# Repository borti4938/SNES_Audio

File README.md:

### SNES Audio Mods
---

This is a collection of earlier projects. These projects are not under development anymore. Documentation is rather simple or simply not present

Please don't write me for any support. Please reach out to community forums and use the knowledge and experiences there.

If you want to change something on the digital audio mod, I suggest you to replace the TI-SPDIF audio encoder by CirrusLogic-SPDIF audio encoder of same size (but different pinout).

Best Regards, Peter

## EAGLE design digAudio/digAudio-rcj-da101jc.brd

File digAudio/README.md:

### IMPORTANT NOTE:

There is a bug on all PCBs manifacture before Jan 5th., 2023!
Pin 14 on the DIT4096 IC is not properly connected.
Instead of tied to GND the pin was left floating.

If you have one effected board, you can easily fix that.
Simply connect pin 14 of the DIT4096 on your PCB to GND.
This pin is a corner pin and you can use any GND pad.
This should be an easy fix.

Sorry for any inconvenience caused! 

-----------------------------------------------------------------------------------

### Solder Joints:

A mapping Pads of PCB to S-DSP/S-APU is given on the bottoms silkscreen.  
Take a picture of it if needed.

-----------------------------------------------------------------------------------

### Components:

See BOM.xlsx (use the appropriate page)  

-----------------------------------------------------------------------------------

### RCA or XLR setup

Design supports both setups. Please be refered to the notes of left in the BOM

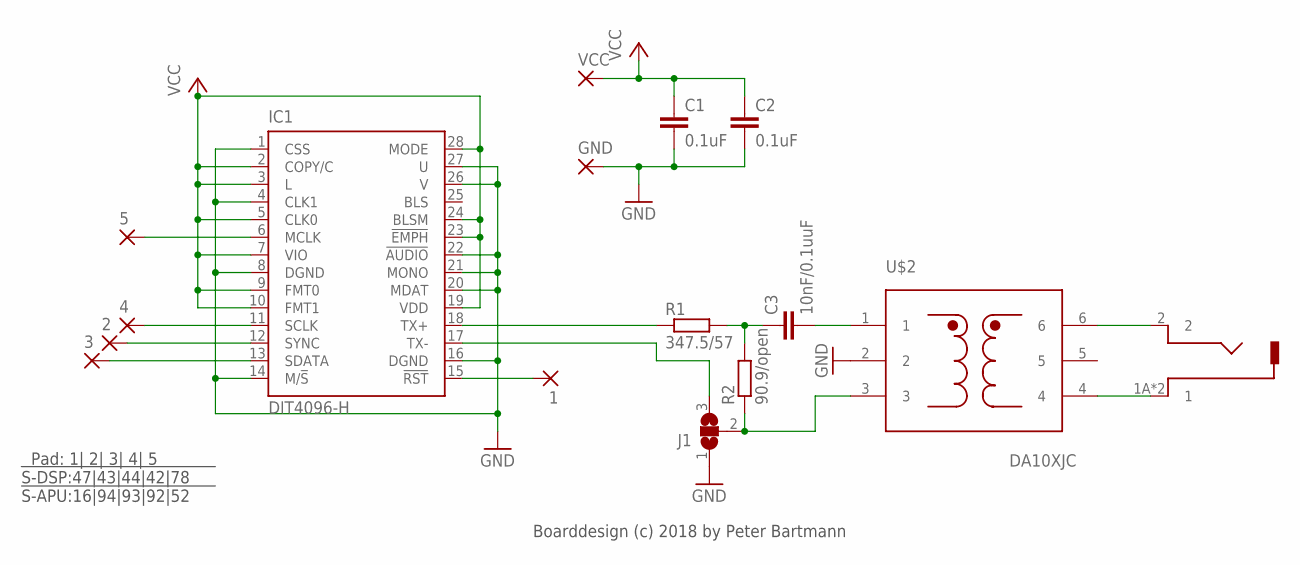
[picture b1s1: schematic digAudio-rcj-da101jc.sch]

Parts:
1, 2, 3, 4, 5: SMD1; SMD0,8-1,6
C1, C2: 0.1uF; C0603
C3: 10nF/0.1uuF; C0603
GND: 1,6/0,9
IC1: DIT4096-H; PW_R-PDSO-G28
J1: SJ2W; SJ_2
R1: 347.5/57; R0603
R2: 90.9/open; R0603
U$1: RCJ-013-SMT-TR; RCJ_01X_SMT_MODIFIED
U$2: DA10XJC; DA101JC
VCC: 1,6/0,9

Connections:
GND: C1.2, C2.2, GND.1, IC1.1 (CSS), IC1.4 (CLK1), IC1.8 (DGND), IC1.14 (M/!S), IC1.16 (DGND), IC1.20 (MDAT), IC1.21 (MONO), IC1.22 (!AUDIO), IC1.26 (V), IC1.27 (U), J1.1, U$2.2
unnamed: IC1.18 (TX+), R1.1
unnamed: 1.P$1, IC1.15 (!RST)
unnamed: 2.P$1, IC1.12 (SYNC)
unnamed: 4.P$1, IC1.11 (SCLK)
unnamed: 3.P$1, IC1.13 (SDATA)
unnamed: 5.P$1, IC1.6 (MCLK)
unnamed: IC1.17 (TX-), J1.3
unnamed: C3.1, R1.2, R2.2
unnamed: U$1.2, U$2.6
unnamed: U$1.1A (1), U$1.1B (1), U$2.4
unnamed: C3.2, U$2.1
unnamed: J1.2, R2.1, U$2.3
VCC: C1.1, C2.1, IC1.2 (COPY/C), IC1.3 (L), IC1.5 (CLK0), IC1.7 (VIO), IC1.9 (FMT0), IC1.10 (FMT1), IC1.19 (VDD), IC1.23 (!EMPH), IC1.24 (BLSM), IC1.28 (MODE), VCC.1

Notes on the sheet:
Pad: 1| 2| 3| 4| 5 S-DSP:47|43|44|42|78 S-APU:16|94|93|92|52
Boarddesign (c) 2018 by Peter Bartmann

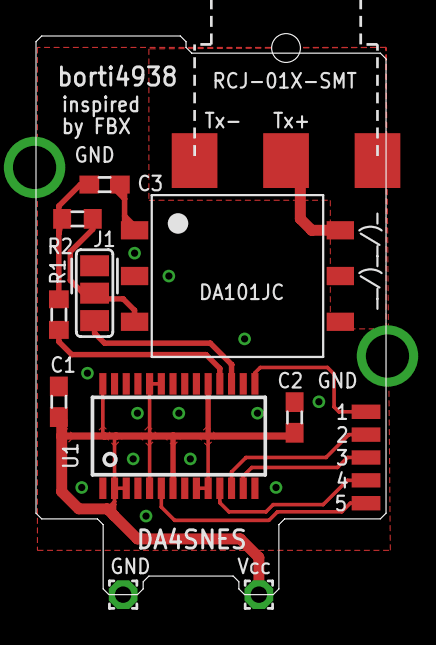
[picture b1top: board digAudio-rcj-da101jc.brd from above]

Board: 2 copper layers, 19.4 x 31.0 mm, 16 parts (0 on the bottom side), 14 nets.

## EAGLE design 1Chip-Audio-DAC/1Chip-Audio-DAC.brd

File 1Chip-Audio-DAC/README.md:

SNES 1Chip Audio DAC replacement
--------------------------------

### Purpose

This board design is suited to replace the 1Chip-SNES audio DAC, which is labeled by U6.  
This board **does not** fixes dead S-MIX, which is U10.

At the moment I don't know whether the boards fits (mechanically) into a SNES model 2 (small form factor SNES)

### Installation

- assemble the board (BOM on bottom silk screen and listed below)
- remove U6
- if you are going to recap your system, you can remove C15 and leave the footprint of C15 unpopulated  
  (it does not hurt to left C15 in place)
- connect the board to the footprint of U6. Check up for adjacent shorts afterwards.  
  (the board do not have to be isolated from bottom as it's a single layer design)
- check for connections at U6:
  - p1: R48 (bottom side mainboard) (audio out right)
  - p2: C15 + (and Vcc through board design)
  - p3: GND
  - p4: R51 (bottom side of mainboard) (audio out left)
  - p5: U2 pin 94 (LRCK)
  - p6: U2 pin 93 (DATA)
  - p7: U2 pin 92 (SCLK)
  - p8: Vcc (+5V)
- connect pad labeld by _U2:52_ with U2 pin 52 (also extension port pin 21)

### BOM

- U1: CS4338-KSZ (SOIC-8 package)
- C1: 0.1uF / 25V+ (SMD 0603 package)
- C2: 1uF /25V+ (SMD 0603 package)

### PCB

Get your PCB from OSHPark or anywhere you like.  
To smoothen the installation, choose a substrate thickness as thin as possible.

## ENJOY!!!

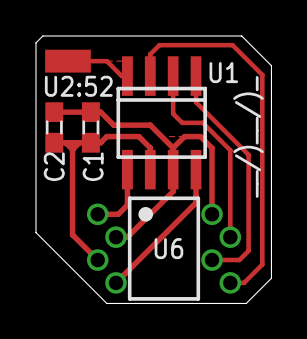
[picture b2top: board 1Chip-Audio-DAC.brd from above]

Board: 2 copper layers, 13.1 x 14.9 mm, 4 parts (0 on the bottom side), 3 nets.

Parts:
C1: 0.1u; C0603
C2: 1u; C0603
MCLK: SMD1,27-2,54
U1: CS4338-KSZ; SO-08

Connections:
AGND: C1.1, C2.1, U1.6
MCLK: MCLK.1, U1.4
VA: C1.2, C2.2, U1.7

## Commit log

2020-05-03 initial commit for archive
2023-01-05 bugfix on PCBs: - pin 14 (M/nS) was floating - now it is properly connected to GND

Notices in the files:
1Chip-Audio-DAC/1Chip-Audio-DAC.brd:
(c) 2018 Peter Bartmann
